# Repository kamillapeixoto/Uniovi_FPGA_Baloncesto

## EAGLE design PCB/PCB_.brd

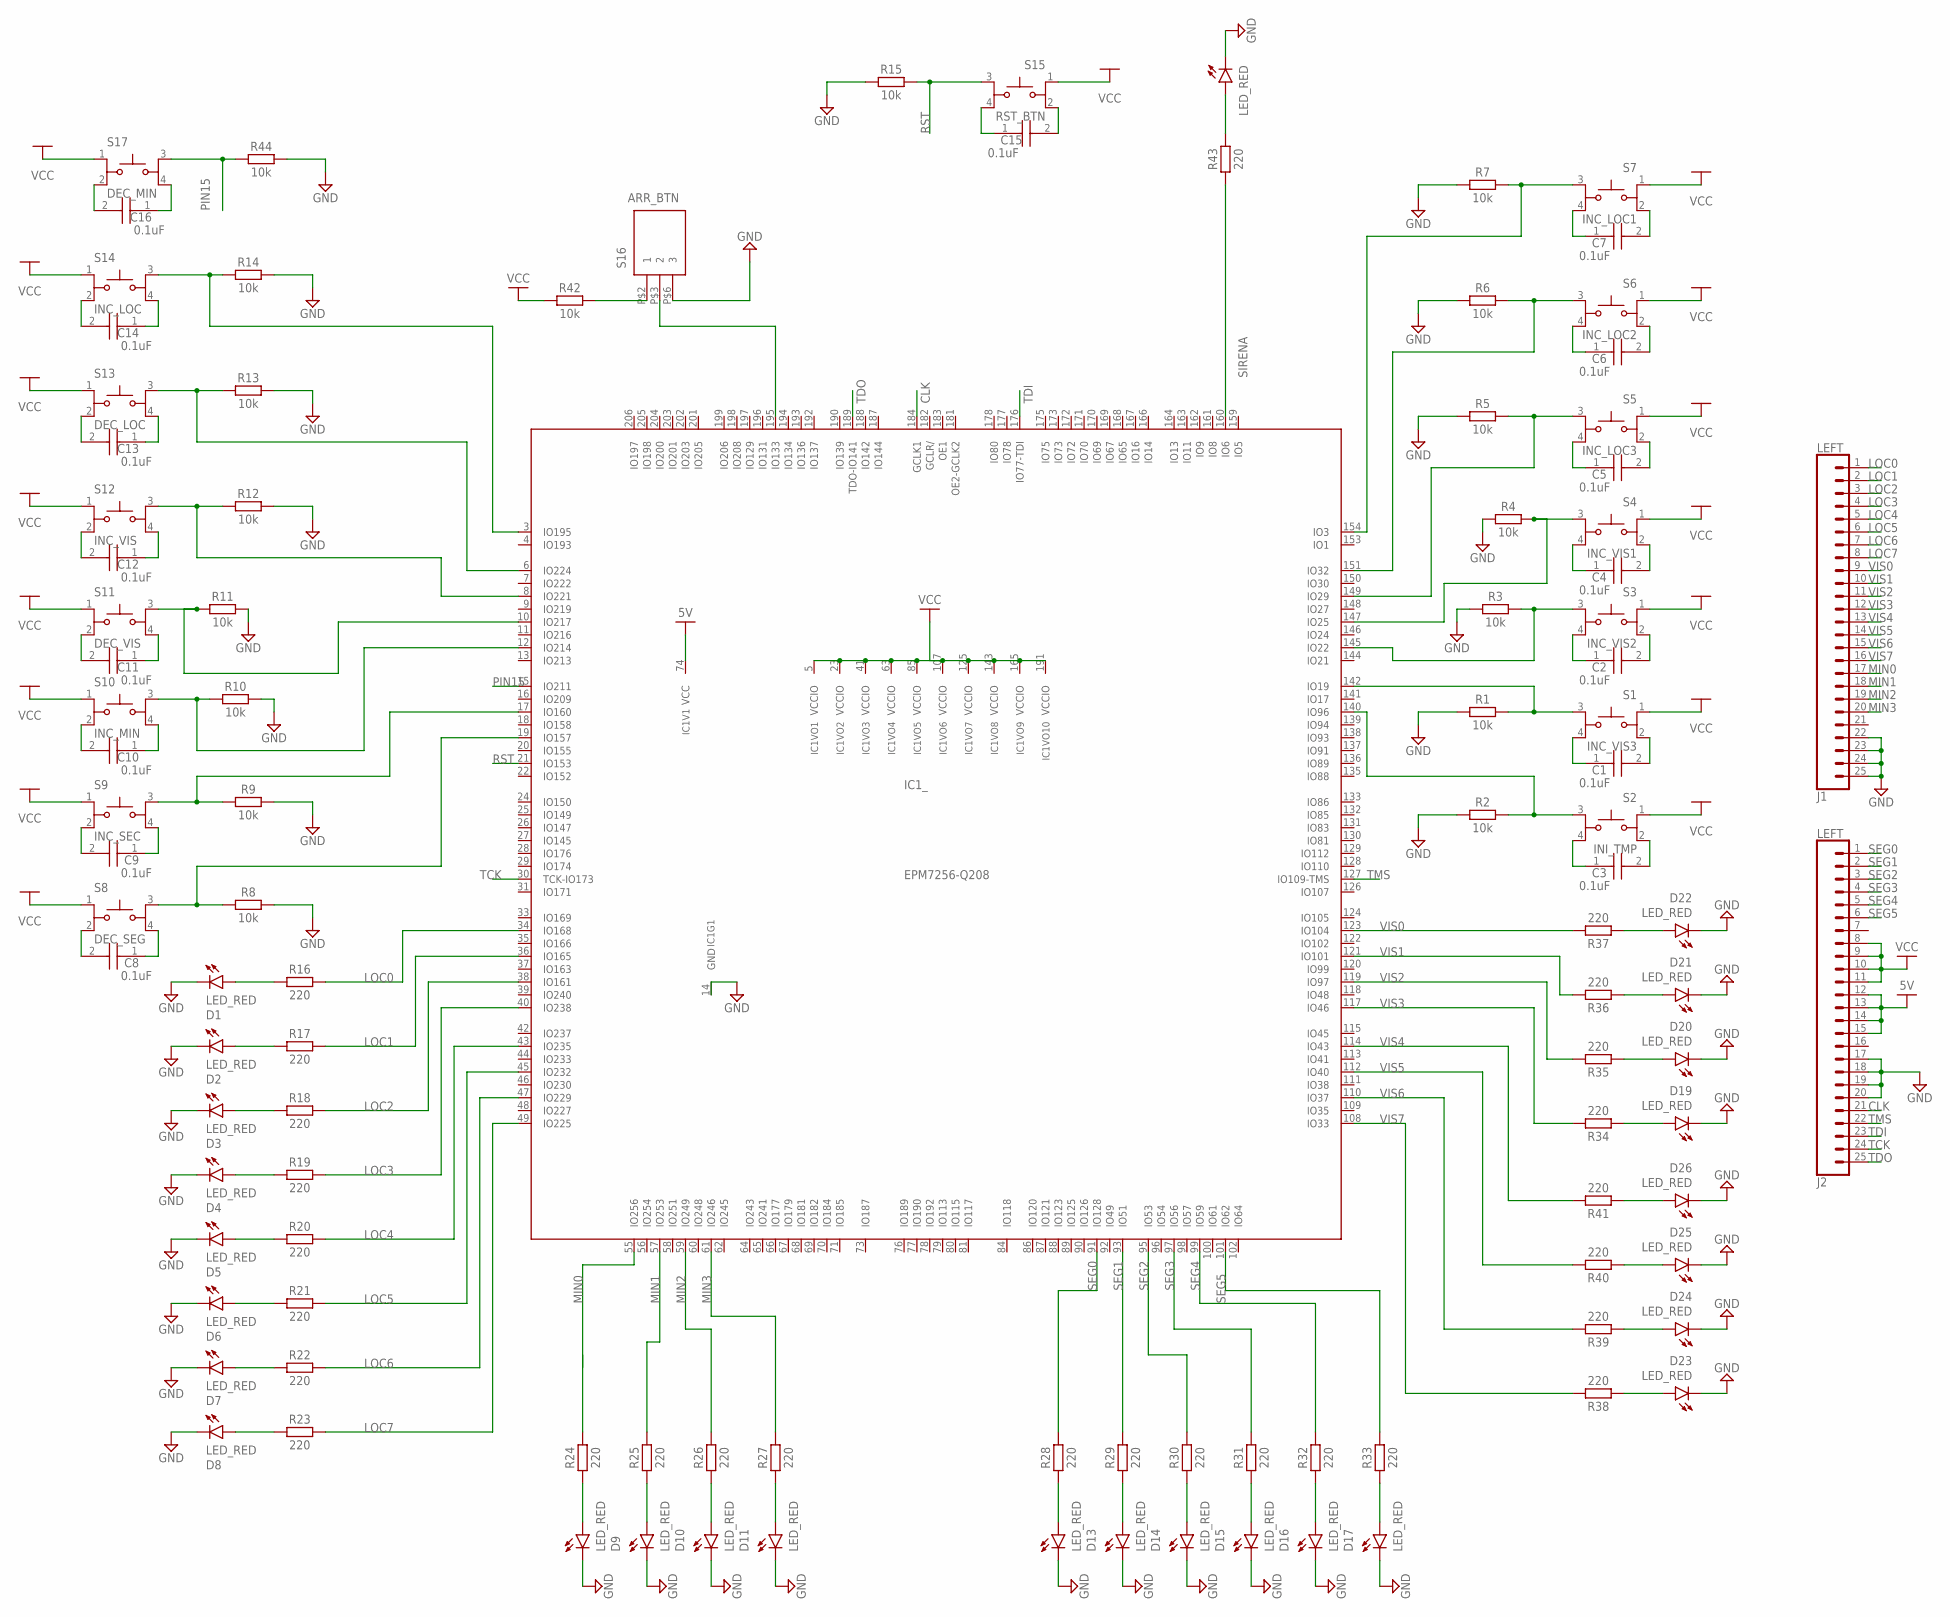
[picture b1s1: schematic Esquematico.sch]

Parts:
C1, C2, C3, C4, C5, C6, C7, C8, C9, C10, C11, C12, C13, C14, C15, C16: 0.1uF; K104K15X7RF53H5
D1, D2, D3, D4, D5, D6, D7, D8, D9, D10, D11, D12, D13, D14, D15, D16, D17, D18, D19, D20, D21, D22, D23, D24, D25, D26, D27: LED_RED; LEDRD254W60D565H860B
IC1: EPM7256-Q208; RQFP208
J1, J2: LEFT; 1X25_LONGPAD
R1, R2, R3, R4, R5, R6, R7, R8, R9, R10, R11, R12, R13, R14, R15, R42, R44: 10k; RESAD724W46L381D178B
R16, R17, R18, R19, R20, R21, R22, R23, R24, R25, R26, R27, R28, R29, R30, R31, R32, R33, R34, R35, R36, R37, R38, R39, R40, R41, R43: 220; RESAD724W46L381D178B
S1: INC_VIS3; SW_TL1100F160Q
S2: INI_TMP; SW_TL1100F160Q
S3: INC_VIS2; SW_TL1100F160Q
S4: INC_VIS1; SW_TL1100F160Q
S5: INC_LOC3; SW_TL1100F160Q
S6: INC_LOC2; SW_TL1100F160Q
S7: INC_LOC1; SW_TL1100F160Q
S8: DEC_SEG; SW_TL1100F160Q
S9: INC_SEC; SW_TL1100F160Q
S10: INC_MIN; SW_TL1100F160Q
S11: DEC_VIS; SW_TL1100F160Q
S12: INC_VIS; SW_TL1100F160Q
S13: DEC_LOC; SW_TL1100F160Q
S14: INC_LOC; SW_TL1100F160Q
S15: RST_BTN; SW_TL1100F160Q
S16: ARR_BTN; 7347306
S17: DEC_MIN; SW_TL1100F160Q

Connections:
5V: IC1.74 (VCC), J2.12, J2.13, J2.14, J2.15
CLK: IC1.184 (GCLK1), J2.21
GND: D1.2 (C), D2.2 (C), D3.2 (C), D4.2 (C), D5.2 (C), D6.2 (C), D7.2 (C), D8.2 (C), D9.2 (C), D10.2 (C), D11.2 (C), D12.2 (C), D13.2 (C), D14.2 (C), D15.2 (C), D16.2 (C), D17.2 (C), D18.2 (C), D19.2 (C), D20.2 (C), D21.2 (C), D22.2 (C), D23.2 (C), D24.2 (C), D25.2 (C), D26.2 (C), D27.2 (C), IC1.14 (GND), IC1.32 (GND), IC1.50 (GND), IC1.72 (GND), IC1.75 (GND), IC1.82 (GND), IC1.94 (GND), IC1.116 (GND), IC1.134 (GND), IC1.152 (GND), IC1.174 (GND), IC1.180 (GND), IC1.185 (GND), IC1.200 (GND), J1.22, J1.23, J1.24, J1.25, J2.17, J2.18, J2.19, J2.20, R1.2, R2.2, R3.2, R4.2, R5.2, R6.2, R7.2, R8.2, R9.2, R10.2, R11.2, R12.2, R13.2, R14.2, R15.2, R44.2, S16.P$6 (3)
LOC0: IC1.34 (IO168), J1.1, R16.1
LOC1: IC1.36 (IO165), J1.2, R17.1
LOC2: IC1.38 (IO161), J1.3, R18.1
LOC3: IC1.40 (IO238), J1.4, R19.1
LOC4: IC1.43 (IO235), J1.5, R20.1
LOC5: IC1.45 (IO232), J1.6, R21.1
LOC6: IC1.47 (IO229), J1.7, R22.1
LOC7: IC1.49 (IO225), J1.8, R23.1
MIN0: IC1.55 (IO256), J1.17, R24.1
MIN1: IC1.57 (IO253), J1.18, R25.1
MIN2: IC1.59 (IO249), J1.19, R26.1
MIN3: IC1.61 (IO246), J1.20, R27.1
unnamed: IC1.3 (IO195), R14.1, S14.3
unnamed: IC1.10 (IO217), R11.1, S11.3
unnamed: IC1.142 (IO19), R1.1, S1.3
unnamed: C1.1, S1.4
unnamed: C1.2, S1.2
unnamed: IC1.140 (IO96), R2.1, S2.3
unnamed: C2.1, S3.4
unnamed: C3.1, S2.4
unnamed: IC1.145 (IO22), R3.1, S3.3
unnamed: C3.2, S2.2
unnamed: C2.2, S3.2
unnamed: IC1.147 (IO25), R4.1, S4.3
unnamed: C4.1, S4.4
unnamed: C4.2, S4.2
unnamed: IC1.8 (IO221), R12.1, S12.3
unnamed: C5.1, S5.4
unnamed: C5.2, S5.2
unnamed: IC1.151 (IO32), R6.1, S6.3
unnamed: IC1.149 (IO29), R5.1, S5.3
unnamed: C6.1, S6.4
unnamed: IC1.19 (IO157), R8.1, S8.3
unnamed: C8.1, S8.4
unnamed: C8.2, S8.2
unnamed: C15.1, S15.4
unnamed: IC1.17 (IO160), R9.1, S9.3
unnamed: C9.1, S9.4
unnamed: C9.2, S9.2
unnamed: C10.1, S10.4
unnamed: C10.2, S10.2
unnamed: C11.1, S11.4
unnamed: C11.2, S11.2
unnamed: C12.1, S12.4
unnamed: C12.2, S12.2
unnamed: IC1.6 (IO224), R13.1, S13.3
unnamed: C13.1, S13.4
unnamed: C13.2, S13.2
unnamed: C15.2, S15.2
unnamed: C14.1, S14.4
unnamed: C16.1, S17.4
unnamed: C14.2, S14.2
unnamed: IC1.12 (IO214), R10.1, S10.3
unnamed: C16.2, S17.2
unnamed: D1.1 (A), R16.2
unnamed: D2.1 (A), R17.2
unnamed: D3.1 (A), R18.2
unnamed: D4.1 (A), R19.2
unnamed: D5.1 (A), R20.2
unnamed: D6.1 (A), R21.2
unnamed: D7.1 (A), R22.2
unnamed: D8.1 (A), R23.2
unnamed: D27.1 (A), R43.2
unnamed: C6.2, S6.2
unnamed: IC1.154 (IO3), R7.1, S7.3
unnamed: C7.1, S7.4
unnamed: C7.2, S7.2
unnamed: D9.1 (A), R24.2
unnamed: D10.1 (A), R25.2
unnamed: D11.1 (A), R26.2
unnamed: D12.1 (A), R27.2
unnamed: D13.1 (A), R28.2
unnamed: D14.1 (A), R29.2
unnamed: D15.1 (A), R30.2
unnamed: D16.1 (A), R31.2
unnamed: D17.1 (A), R32.2
unnamed: D18.1 (A), R33.2
unnamed: D19.1 (A), R34.2
unnamed: D20.1 (A), R35.2
unnamed: D21.1 (A), R36.2
unnamed: D22.1 (A), R37.2
unnamed: D23.1 (A), R38.2
unnamed: D24.1 (A), R39.2
unnamed: D25.1 (A), R40.2
unnamed: D26.1 (A), R41.2
unnamed: IC1.195 (IO133), S16.P$3 (2)
unnamed: R42.1, S16.P$2 (1)
PIN15: IC1.15 (IO211), R44.1, S17.3
RST: IC1.21 (IO153), R15.1, S15.3
SEG0: IC1.91 (IO128), J2.1, R28.1
SEG1: IC1.93 (IO51), J2.2, R29.1
SEG2: IC1.95 (IO53), J2.3, R30.1
SEG3: IC1.97 (IO56), J2.4, R31.1
SEG4: IC1.99 (IO59), J2.5, R32.1
SEG5: IC1.101 (IO62), J2.6, R33.1
SIRENA: IC1.160 (IO6), R43.1
TCK: IC1.30 (TCK-IO173), J2.24
TDI: IC1.176 (IO77-TDI), J2.23
TDO: IC1.189 (TDO-IO141), J2.25
TMS: IC1.127 (IO109-TMS), J2.22
VCC: IC1.5 (VCCIO), IC1.23 (VCCIO), IC1.41 (VCCIO), IC1.63 (VCCIO), IC1.83 (VCC), IC1.85 (VCCIO), IC1.107 (VCCIO), IC1.125 (VCCIO), IC1.143 (VCCIO), IC1.165 (VCCIO), IC1.179 (VCC), IC1.186 (VCC), IC1.191 (VCCIO), J2.8, J2.9, J2.10, J2.11, R42.2, S1.1, S2.1, S3.1, S4.1, S5.1, S6.1, S7.1, S8.1, S9.1, S10.1, S11.1, S12.1, S13.1, S14.1, S15.1, S17.1
VIS0: IC1.123 (IO104), J1.9, R37.1
VIS1: IC1.121 (IO101), J1.10, R36.1
VIS2: IC1.119 (IO97), J1.11, R35.1
VIS3: IC1.117 (IO46), J1.12, R34.1
VIS4: IC1.114 (IO43), J1.13, R41.1
VIS5: IC1.112 (IO40), J1.14, R40.1
VIS6: IC1.110 (IO37), J1.15, R39.1
VIS7: IC1.108 (IO33), J1.16, R38.1

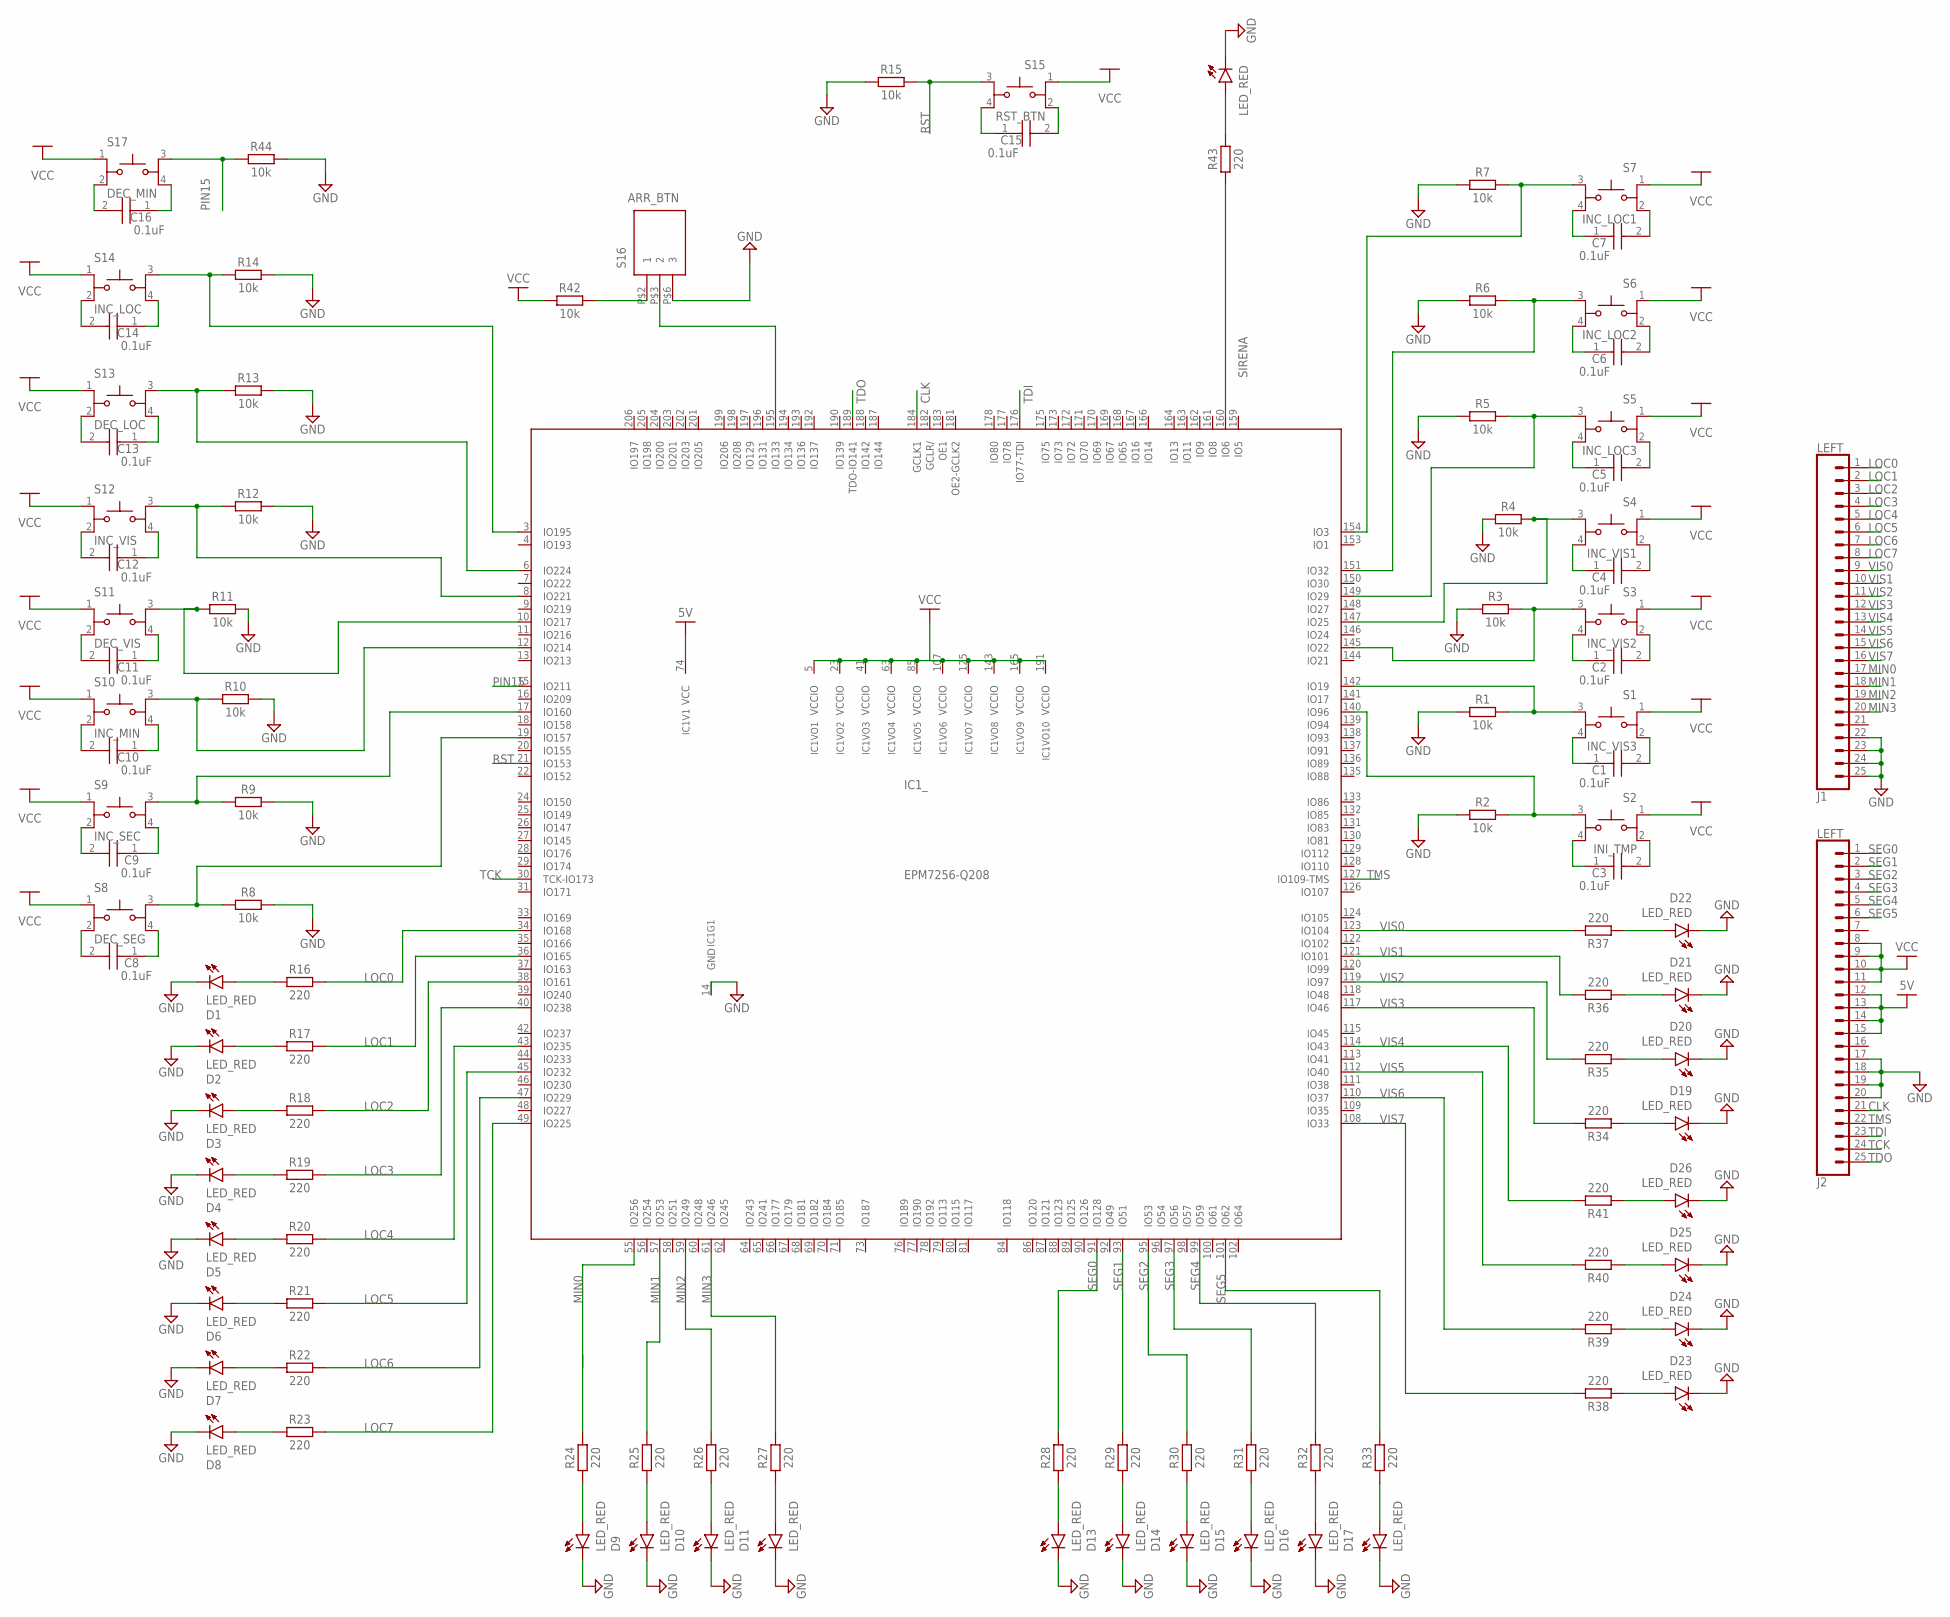
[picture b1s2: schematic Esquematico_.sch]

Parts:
C1, C2, C3, C4, C5, C6, C7, C8, C9, C10, C11, C12, C13, C14, C15, C16: 0.1uF; K104K15X7RF53H5
D1, D2, D3, D4, D5, D6, D7, D8, D9, D10, D11, D12, D13, D14, D15, D16, D17, D18, D19, D20, D21, D22, D23, D24, D25, D26, D27: LED_RED; LEDRD254W60D565H860B
IC1: EPM7256-Q208; RQFP208
J1, J2: LEFT; 1X25_LONGPAD
R1, R2, R3, R4, R5, R6, R7, R8, R9, R10, R11, R12, R13, R14, R15, R42, R44: 10k; RESAD724W46L381D178B
R16, R17, R18, R19, R20, R21, R22, R23, R24, R25, R26, R27, R28, R29, R30, R31, R32, R33, R34, R35, R36, R37, R38, R39, R40, R41, R43: 220; RESAD724W46L381D178B
S1: INC_VIS3; SW_TL1100F160Q
S2: INI_TMP; SW_TL1100F160Q
S3: INC_VIS2; SW_TL1100F160Q
S4: INC_VIS1; SW_TL1100F160Q
S5: INC_LOC3; SW_TL1100F160Q
S6: INC_LOC2; SW_TL1100F160Q
S7: INC_LOC1; SW_TL1100F160Q
S8: DEC_SEG; SW_TL1100F160Q
S9: INC_SEC; SW_TL1100F160Q
S10: INC_MIN; SW_TL1100F160Q
S11: DEC_VIS; SW_TL1100F160Q
S12: INC_VIS; SW_TL1100F160Q
S13: DEC_LOC; SW_TL1100F160Q
S14: INC_LOC; SW_TL1100F160Q
S15: RST_BTN; SW_TL1100F160Q
S16: ARR_BTN; 7347306
S17: DEC_MIN; SW_TL1100F160Q

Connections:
5V: IC1.74 (VCC), J2.12, J2.13, J2.14, J2.15
CLK: IC1.184 (GCLK1), J2.21
GND: D1.2 (C), D2.2 (C), D3.2 (C), D4.2 (C), D5.2 (C), D6.2 (C), D7.2 (C), D8.2 (C), D9.2 (C), D10.2 (C), D11.2 (C), D12.2 (C), D13.2 (C), D14.2 (C), D15.2 (C), D16.2 (C), D17.2 (C), D18.2 (C), D19.2 (C), D20.2 (C), D21.2 (C), D22.2 (C), D23.2 (C), D24.2 (C), D25.2 (C), D26.2 (C), D27.2 (C), IC1.14 (GND), IC1.32 (GND), IC1.50 (GND), IC1.72 (GND), IC1.75 (GND), IC1.82 (GND), IC1.94 (GND), IC1.116 (GND), IC1.134 (GND), IC1.152 (GND), IC1.174 (GND), IC1.180 (GND), IC1.185 (GND), IC1.200 (GND), J1.22, J1.23, J1.24, J1.25, J2.17, J2.18, J2.19, J2.20, R1.2, R2.2, R3.2, R4.2, R5.2, R6.2, R7.2, R8.2, R9.2, R10.2, R11.2, R12.2, R13.2, R14.2, R15.2, R44.2, S16.P$6 (3)
LOC0: IC1.34 (IO168), J1.1, R16.1
LOC1: IC1.36 (IO165), J1.2, R17.1
LOC2: IC1.38 (IO161), J1.3, R18.1
LOC3: IC1.40 (IO238), J1.4, R19.1
LOC4: IC1.43 (IO235), J1.5, R20.1
LOC5: IC1.45 (IO232), J1.6, R21.1
LOC6: IC1.47 (IO229), J1.7, R22.1
LOC7: IC1.49 (IO225), J1.8, R23.1
MIN0: IC1.55 (IO256), J1.17, R24.1
MIN1: IC1.57 (IO253), J1.18, R25.1
MIN2: IC1.59 (IO249), J1.19, R26.1
MIN3: IC1.61 (IO246), J1.20, R27.1
unnamed: IC1.3 (IO195), R14.1, S14.3
unnamed: IC1.10 (IO217), R11.1, S11.3
unnamed: IC1.142 (IO19), R1.1, S1.3
unnamed: C1.1, S1.4
unnamed: C1.2, S1.2
unnamed: IC1.140 (IO96), R2.1, S2.3
unnamed: C2.1, S3.4
unnamed: C3.1, S2.4
unnamed: IC1.145 (IO22), R3.1, S3.3
unnamed: C3.2, S2.2
unnamed: C2.2, S3.2
unnamed: IC1.147 (IO25), R4.1, S4.3
unnamed: C4.1, S4.4
unnamed: C4.2, S4.2
unnamed: IC1.8 (IO221), R12.1, S12.3
unnamed: C5.1, S5.4
unnamed: C5.2, S5.2
unnamed: IC1.151 (IO32), R6.1, S6.3
unnamed: IC1.149 (IO29), R5.1, S5.3
unnamed: C6.1, S6.4
unnamed: IC1.19 (IO157), R8.1, S8.3
unnamed: C8.1, S8.4
unnamed: C8.2, S8.2
unnamed: C15.1, S15.4
unnamed: IC1.17 (IO160), R9.1, S9.3
unnamed: C9.1, S9.4
unnamed: C9.2, S9.2
unnamed: C10.1, S10.4
unnamed: C10.2, S10.2
unnamed: C11.1, S11.4
unnamed: C11.2, S11.2
unnamed: C12.1, S12.4
unnamed: C12.2, S12.2
unnamed: IC1.6 (IO224), R13.1, S13.3
unnamed: C13.1, S13.4
unnamed: C13.2, S13.2
unnamed: C15.2, S15.2
unnamed: C14.1, S14.4
unnamed: C16.1, S17.4
unnamed: C14.2, S14.2
unnamed: IC1.12 (IO214), R10.1, S10.3
unnamed: C16.2, S17.2
unnamed: D1.1 (A), R16.2
unnamed: D2.1 (A), R17.2
unnamed: D3.1 (A), R18.2
unnamed: D4.1 (A), R19.2
unnamed: D5.1 (A), R20.2
unnamed: D6.1 (A), R21.2
unnamed: D7.1 (A), R22.2
unnamed: D8.1 (A), R23.2
unnamed: D27.1 (A), R43.2
unnamed: C6.2, S6.2
unnamed: IC1.154 (IO3), R7.1, S7.3
unnamed: C7.1, S7.4
unnamed: C7.2, S7.2
unnamed: D9.1 (A), R24.2
unnamed: D10.1 (A), R25.2
unnamed: D11.1 (A), R26.2
unnamed: D12.1 (A), R27.2
unnamed: D13.1 (A), R28.2
unnamed: D14.1 (A), R29.2
unnamed: D15.1 (A), R30.2
unnamed: D16.1 (A), R31.2
unnamed: D17.1 (A), R32.2
unnamed: D18.1 (A), R33.2
unnamed: D19.1 (A), R34.2
unnamed: D20.1 (A), R35.2
unnamed: D21.1 (A), R36.2
unnamed: D22.1 (A), R37.2
unnamed: D23.1 (A), R38.2
unnamed: D24.1 (A), R39.2
unnamed: D25.1 (A), R40.2
unnamed: D26.1 (A), R41.2
unnamed: IC1.195 (IO133), S16.P$3 (2)
unnamed: R42.1, S16.P$2 (1)
PIN15: IC1.15 (IO211), R44.1, S17.3
RST: IC1.21 (IO153), R15.1, S15.3
SEG0: IC1.91 (IO128), J2.1, R28.1
SEG1: IC1.93 (IO51), J2.2, R29.1
SEG2: IC1.95 (IO53), J2.3, R30.1
SEG3: IC1.97 (IO56), J2.4, R31.1
SEG4: IC1.99 (IO59), J2.5, R32.1
SEG5: IC1.101 (IO62), J2.6, R33.1
SIRENA: IC1.160 (IO6), R43.1
TCK: IC1.30 (TCK-IO173), J2.24
TDI: IC1.176 (IO77-TDI), J2.23
TDO: IC1.189 (TDO-IO141), J2.25
TMS: IC1.127 (IO109-TMS), J2.22
VCC: IC1.5 (VCCIO), IC1.23 (VCCIO), IC1.41 (VCCIO), IC1.63 (VCCIO), IC1.83 (VCC), IC1.85 (VCCIO), IC1.107 (VCCIO), IC1.125 (VCCIO), IC1.143 (VCCIO), IC1.165 (VCCIO), IC1.179 (VCC), IC1.186 (VCC), IC1.191 (VCCIO), J2.8, J2.9, J2.10, J2.11, R42.2, S1.1, S2.1, S3.1, S4.1, S5.1, S6.1, S7.1, S8.1, S9.1, S10.1, S11.1, S12.1, S13.1, S14.1, S15.1, S17.1
VIS0: IC1.123 (IO104), J1.9, R37.1
VIS1: IC1.121 (IO101), J1.10, R36.1
VIS2: IC1.119 (IO97), J1.11, R35.1
VIS3: IC1.117 (IO46), J1.12, R34.1
VIS4: IC1.114 (IO43), J1.13, R41.1
VIS5: IC1.112 (IO40), J1.14, R40.1
VIS6: IC1.110 (IO37), J1.15, R39.1
VIS7: IC1.108 (IO33), J1.16, R38.1

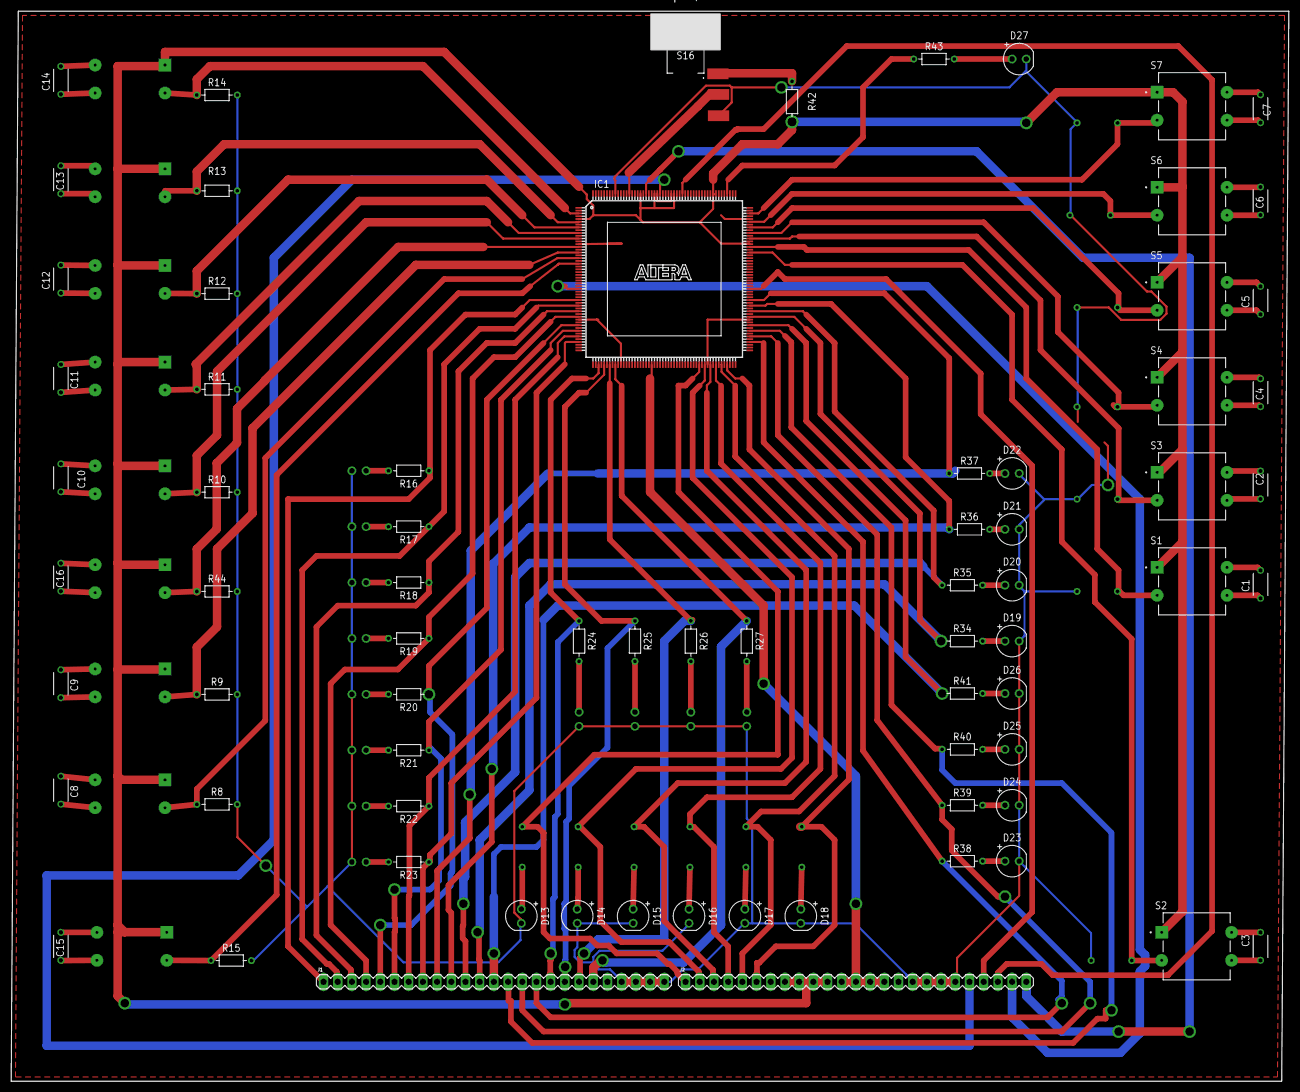
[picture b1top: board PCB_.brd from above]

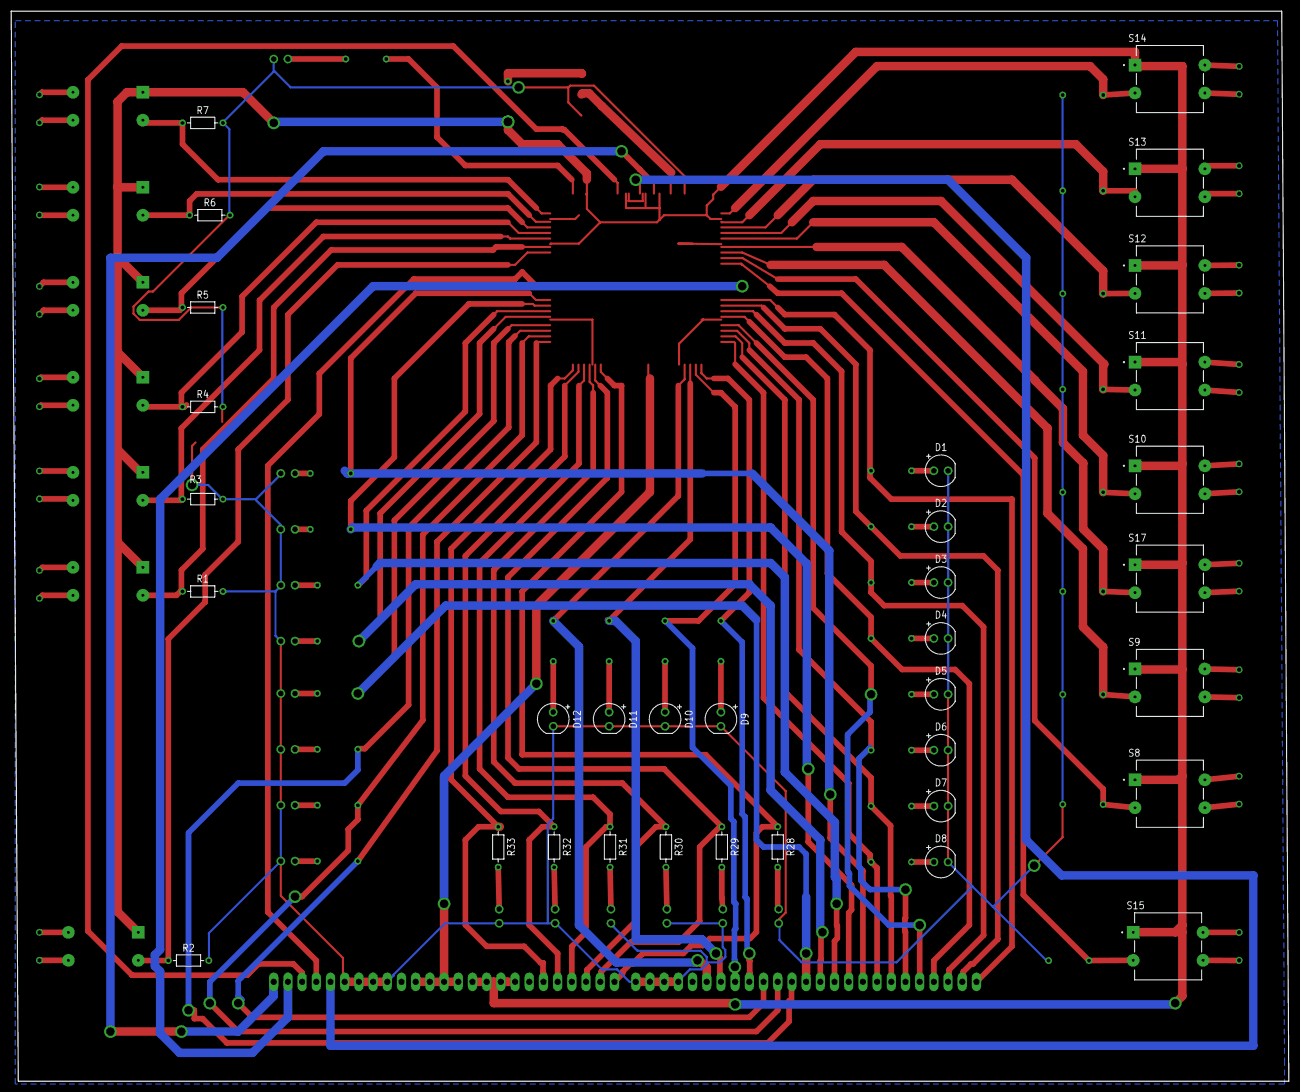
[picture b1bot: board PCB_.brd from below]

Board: 2 copper layers, 228.6 x 191.4 mm, 107 parts (34 on the bottom side), 112 nets.

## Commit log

2023-05-13 Version Completa
2023-05-13 Version completa
    Eliminacion de archivos desnecesarios
2023-05-19 Ready
2023-05-20 final

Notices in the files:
parts and their libraries:
SparkFun-Connectors: Licensing: Creative Commons ShareAlike 4.0 International - https://creativecommons.org/licenses/by-sa/4.0
